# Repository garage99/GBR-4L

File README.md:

# GBR-4L

GBR-4L is a self-powered USB 2.0 carrier for four Semtech (formerly Sierra
Wireless) AirPrime EM7565 LTE modules. It is intended for use with
OpenMPTCProuter and for manufacture by JLCPCB.

## Rev 1.0 baseline

- Four EM7565 modules in M.2 Key B 3042 sockets
- One nano-SIM per modem
- USB 2.0 High-Speed upstream through a USB Type-C receptacle
- Four-port USB 2.0 hub
- 12 V external input
- Four independently controlled 3.3 V modem power rails
- Per-modem `RESET#`, `W_DISABLE1#`, status indication, and test points
- Four-layer PCB: signal / ground / power / signal
- Preferred outline: 160 mm x 100 mm

> EM7565 is an M.2 module, not a Mini PCIe card. The USB Type-C connector is an
> upstream-facing USB device port (UFP), even though it connects to the host PC.

## Repository layout

- `Hardware/KiCad/GBR-4L/` — KiCad 10 project
- `Hardware/Design/` — requirements, design decisions, and interface definitions
- `Hardware/BOM/` — preliminary and released bills of materials
- `Firmware/` — reserved for optional control firmware
- `Case/` — enclosure and mechanical data

## Current milestone

M1 (part selection and electrical architecture) is in progress. The initial
architecture is recorded in
[`Hardware/Design/GBR-4L_Rev1_Design_Baseline.md`](Hardware/Design/GBR-4L_Rev1_Design_Baseline.md).
No Gerber files are released yet.

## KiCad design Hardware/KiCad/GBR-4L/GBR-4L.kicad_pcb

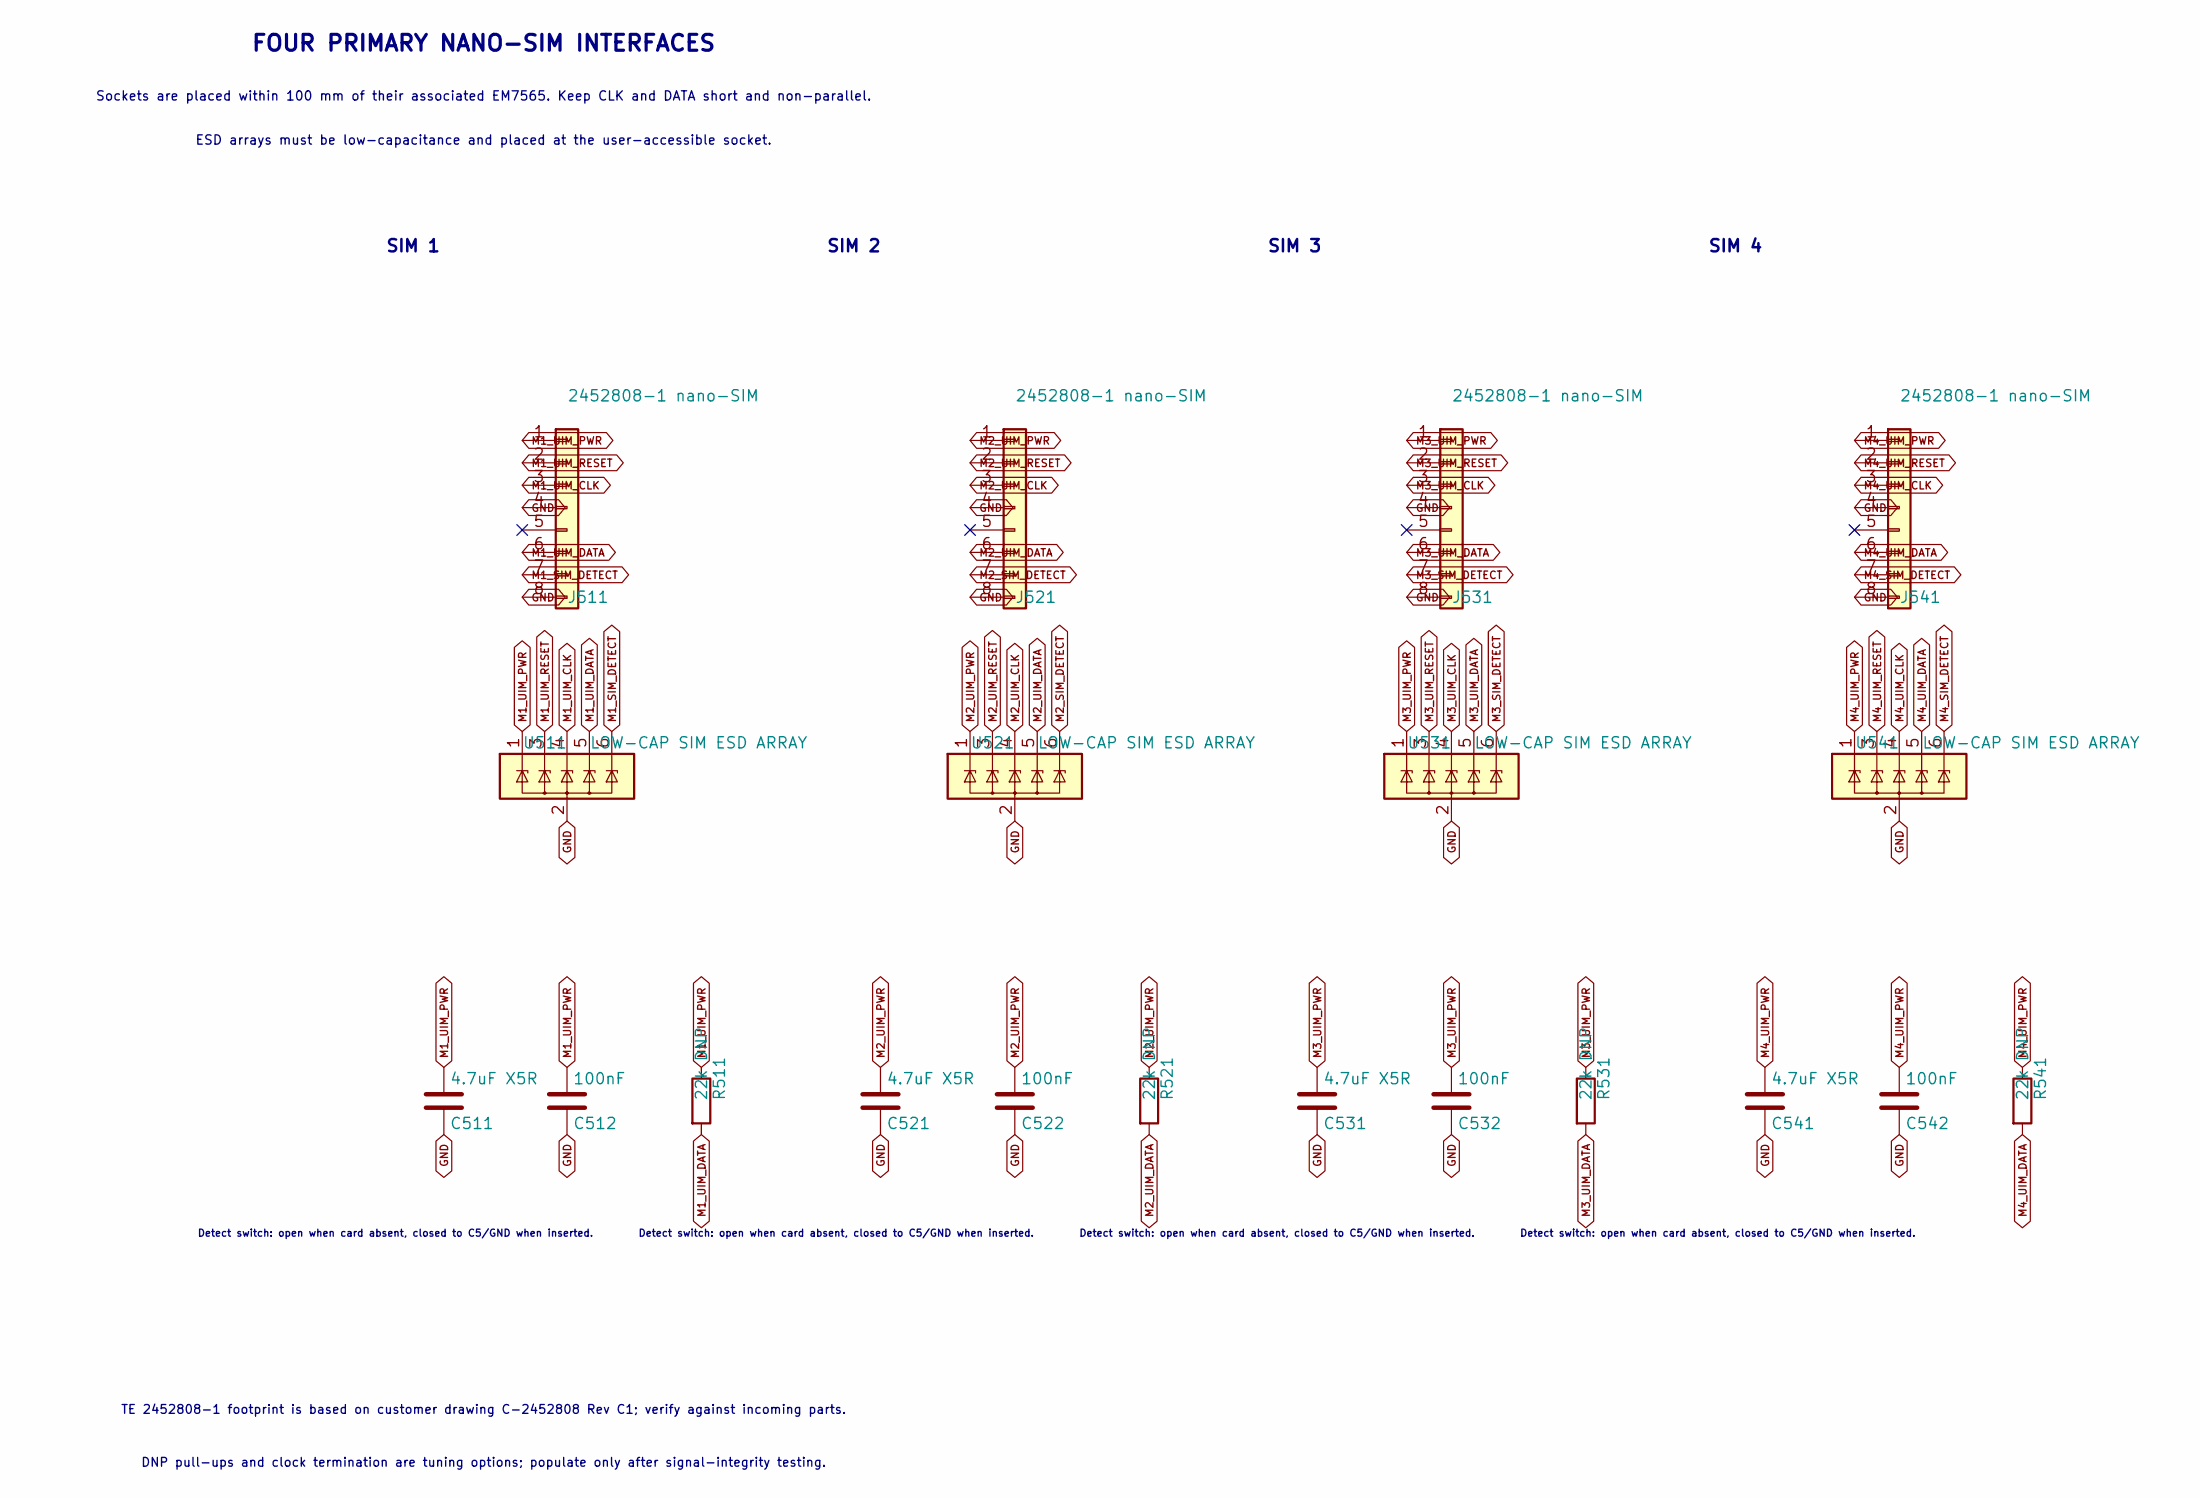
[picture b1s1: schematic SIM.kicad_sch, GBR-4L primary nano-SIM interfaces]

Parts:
C511, C521, C531, C541: 4.7uF X5R; C_0805_2012Metric
C512, C522, C532, C542: 100nF; C_0603_1608Metric
J511, J521, J531, J541: 2452808-1 nano-SIM; TE_2452808-1
R511, R521, R531, R541: 22k DNP; R_0603_1608Metric
U511, U521, U531, U541: LOW-CAP SIM ESD ARRAY; SOT-23-6

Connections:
GND: C511.2, C512.2, C521.2, C522.2, C531.2, C532.2, C541.2, C542.2, J511.4, J511.8, J511.9, J511.10, J511.11, J521.4, J521.8, J521.9, J521.10, J521.11, J531.4, J531.8, J531.9, J531.10, J531.11, J541.4, J541.8, J541.9, J541.10, J541.11, U511.2 (GND), U521.2 (GND), U531.2 (GND), U541.2 (GND); also elsewhere on the board
M1_SIM_DETECT: J511.7, U511.6 (IO5); also elsewhere on the board
M1_UIM_CLK: J511.3, U511.4 (IO3); also elsewhere on the board
M1_UIM_DATA: J511.6, R511.2, U511.5 (IO4); also elsewhere on the board
M1_UIM_PWR: C511.1, C512.1, J511.1, R511.1, U511.1 (IO1); also elsewhere on the board
M1_UIM_RESET: J511.2, U511.3 (IO2); also elsewhere on the board
M2_SIM_DETECT: J521.7, U521.6 (IO5); also elsewhere on the board
M2_UIM_CLK: J521.3, U521.4 (IO3); also elsewhere on the board
M2_UIM_DATA: J521.6, R521.2, U521.5 (IO4); also elsewhere on the board
M2_UIM_PWR: C521.1, C522.1, J521.1, R521.1, U521.1 (IO1); also elsewhere on the board
M2_UIM_RESET: J521.2, U521.3 (IO2); also elsewhere on the board
M3_SIM_DETECT: J531.7, U531.6 (IO5); also elsewhere on the board
M3_UIM_CLK: J531.3, U531.4 (IO3); also elsewhere on the board
M3_UIM_DATA: J531.6, R531.2, U531.5 (IO4); also elsewhere on the board
M3_UIM_PWR: C531.1, C532.1, J531.1, R531.1, U531.1 (IO1); also elsewhere on the board
M3_UIM_RESET: J531.2, U531.3 (IO2); also elsewhere on the board
M4_SIM_DETECT: J541.7, U541.6 (IO5); also elsewhere on the board
M4_UIM_CLK: J541.3, U541.4 (IO3); also elsewhere on the board
M4_UIM_DATA: J541.6, R541.2, U541.5 (IO4); also elsewhere on the board
M4_UIM_PWR: C541.1, C542.1, J541.1, R541.1, U541.1 (IO1); also elsewhere on the board
M4_UIM_RESET: J541.2, U541.3 (IO2); also elsewhere on the board

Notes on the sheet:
SIM 3
ESD arrays must be low-capacitance and placed at the user-accessible socket.
SIM 4
FOUR PRIMARY NANO-SIM INTERFACES
Sockets are placed within 100 mm of their associated EM7565. Keep CLK and DATA short and non-parallel.
SIM 2
Detect switch: open when card absent, closed to C5/GND when inserted.
DNP pull-ups and clock termination are tuning options; populate only after signal-integrity testing.
SIM 1
TE 2452808-1 footprint is based on customer drawing C-2452808 Rev C1; verify against incoming parts.

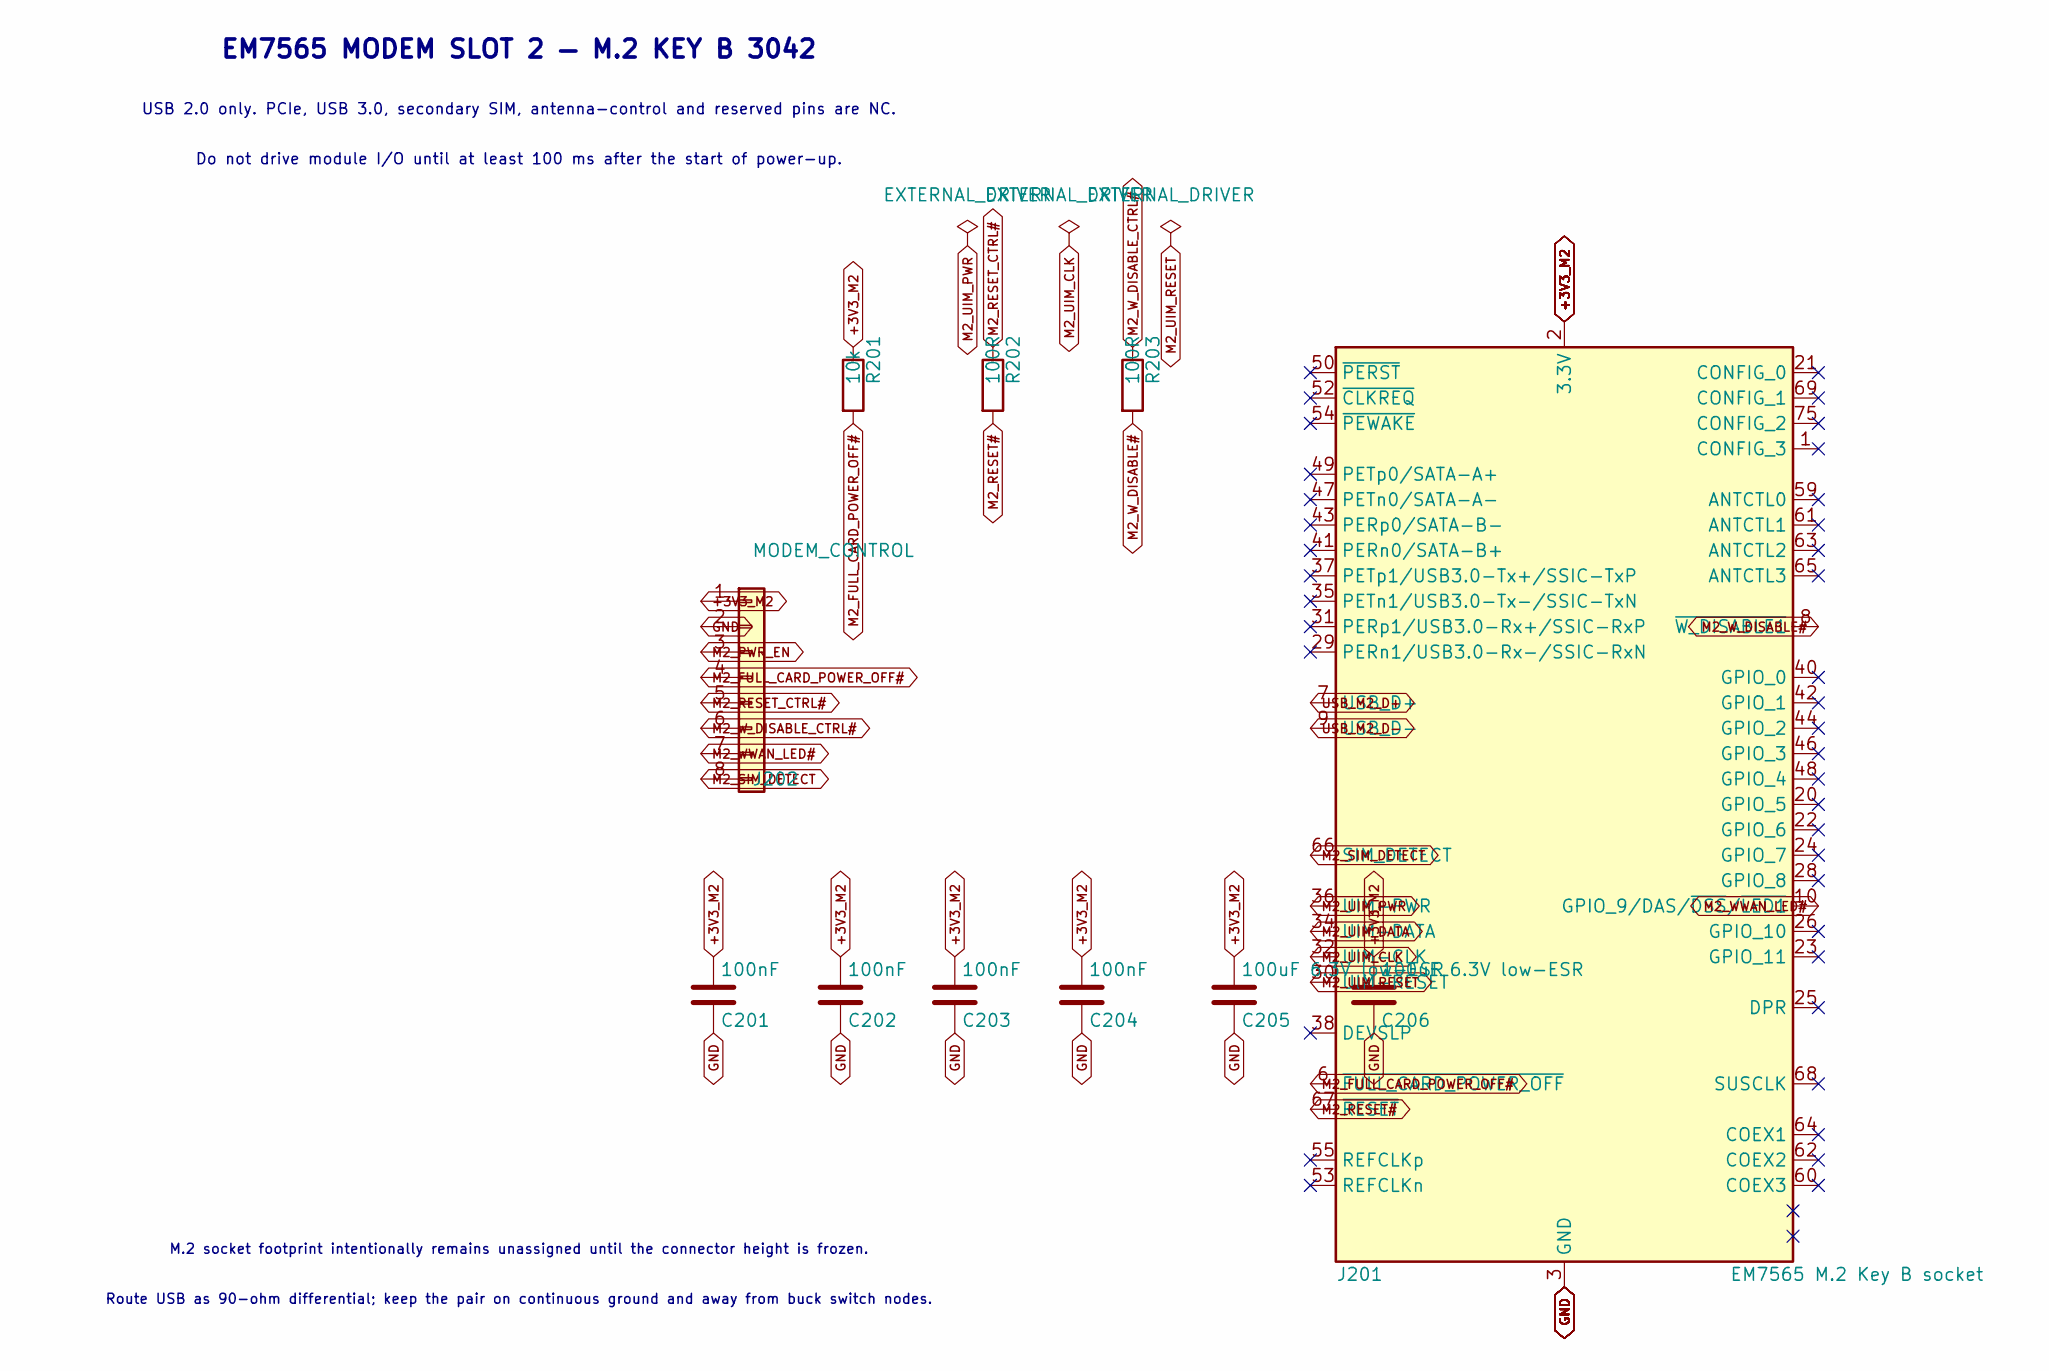
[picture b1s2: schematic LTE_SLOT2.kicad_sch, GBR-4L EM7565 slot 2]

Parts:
C201, C202, C203, C204: 100nF; C_0603_1608Metric
C205, C206: 100uF 6.3V low-ESR; C_1210_3225Metric
J201: EM7565 M.2 Key B socket
J202: MODEM_CONTROL; PinHeader_1x08_P2.54mm_Vertical
R201: 10k; R_0603_1608Metric
R202, R203: 100R; R_0603_1608Metric

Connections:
+3V3_M2: C201.1, C202.1, C203.1, C204.1, C205.1, C206.1, J201.2 (3.3V), J201.4 (3.3V), J201.70 (3.3V), J201.72 (3.3V), J201.74 (3.3V), J202.1, R201.1; also elsewhere on the board
GND: C201.2, C202.2, C203.2, C204.2, C205.2, C206.2, J201.3 (GND), J201.5 (GND), J201.11 (GND), J201.27 (GND), J201.33 (GND), J201.39 (GND), J201.45 (GND), J201.51 (GND), J201.57 (GND), J201.71 (GND), J201.73 (GND), J202.2; also elsewhere on the board
M2_FULL_CARD_POWER_OFF#: J201.6 (~FULL_CARD_POWER_OFF), J202.4, R201.2
M2_PWR_EN: J202.3; also elsewhere on the board
M2_RESET#: J201.67 (~RESET), R202.2
M2_RESET_CTRL#: J202.5, R202.1; also elsewhere on the board
M2_SIM_DETECT: J201.66 (SIM_DETECT), J202.8; also elsewhere on the board
M2_UIM_CLK: J201.32 (UIM-CLK); also elsewhere on the board
M2_UIM_DATA: J201.34 (UIM-DATA); also elsewhere on the board
M2_UIM_PWR: J201.36 (UIM-PWR); also elsewhere on the board
M2_UIM_RESET: J201.30 (UIM-RESET); also elsewhere on the board
M2_WWAN_LED#: J201.10 (GPIO_9/DAS/~DSS/~LED1), J202.7; also elsewhere on the board
M2_W_DISABLE#: J201.8 (~W_DISABLE1), R203.2
M2_W_DISABLE_CTRL#: J202.6, R203.1; also elsewhere on the board
USB_M2_D+: J201.7 (USB_D+); also elsewhere on the board
USB_M2_D-: J201.9 (USB_D-); also elsewhere on the board

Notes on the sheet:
Route USB as 90-ohm differential; keep the pair on continuous ground and away from buck switch nodes.
USB 2.0 only. PCIe, USB 3.0, secondary SIM, antenna-control and reserved pins are NC.
M.2 socket footprint intentionally remains unassigned until the connector height is frozen.
Do not drive module I/O until at least 100 ms after the start of power-up.
EM7565 MODEM SLOT 2 — M.2 KEY B 3042

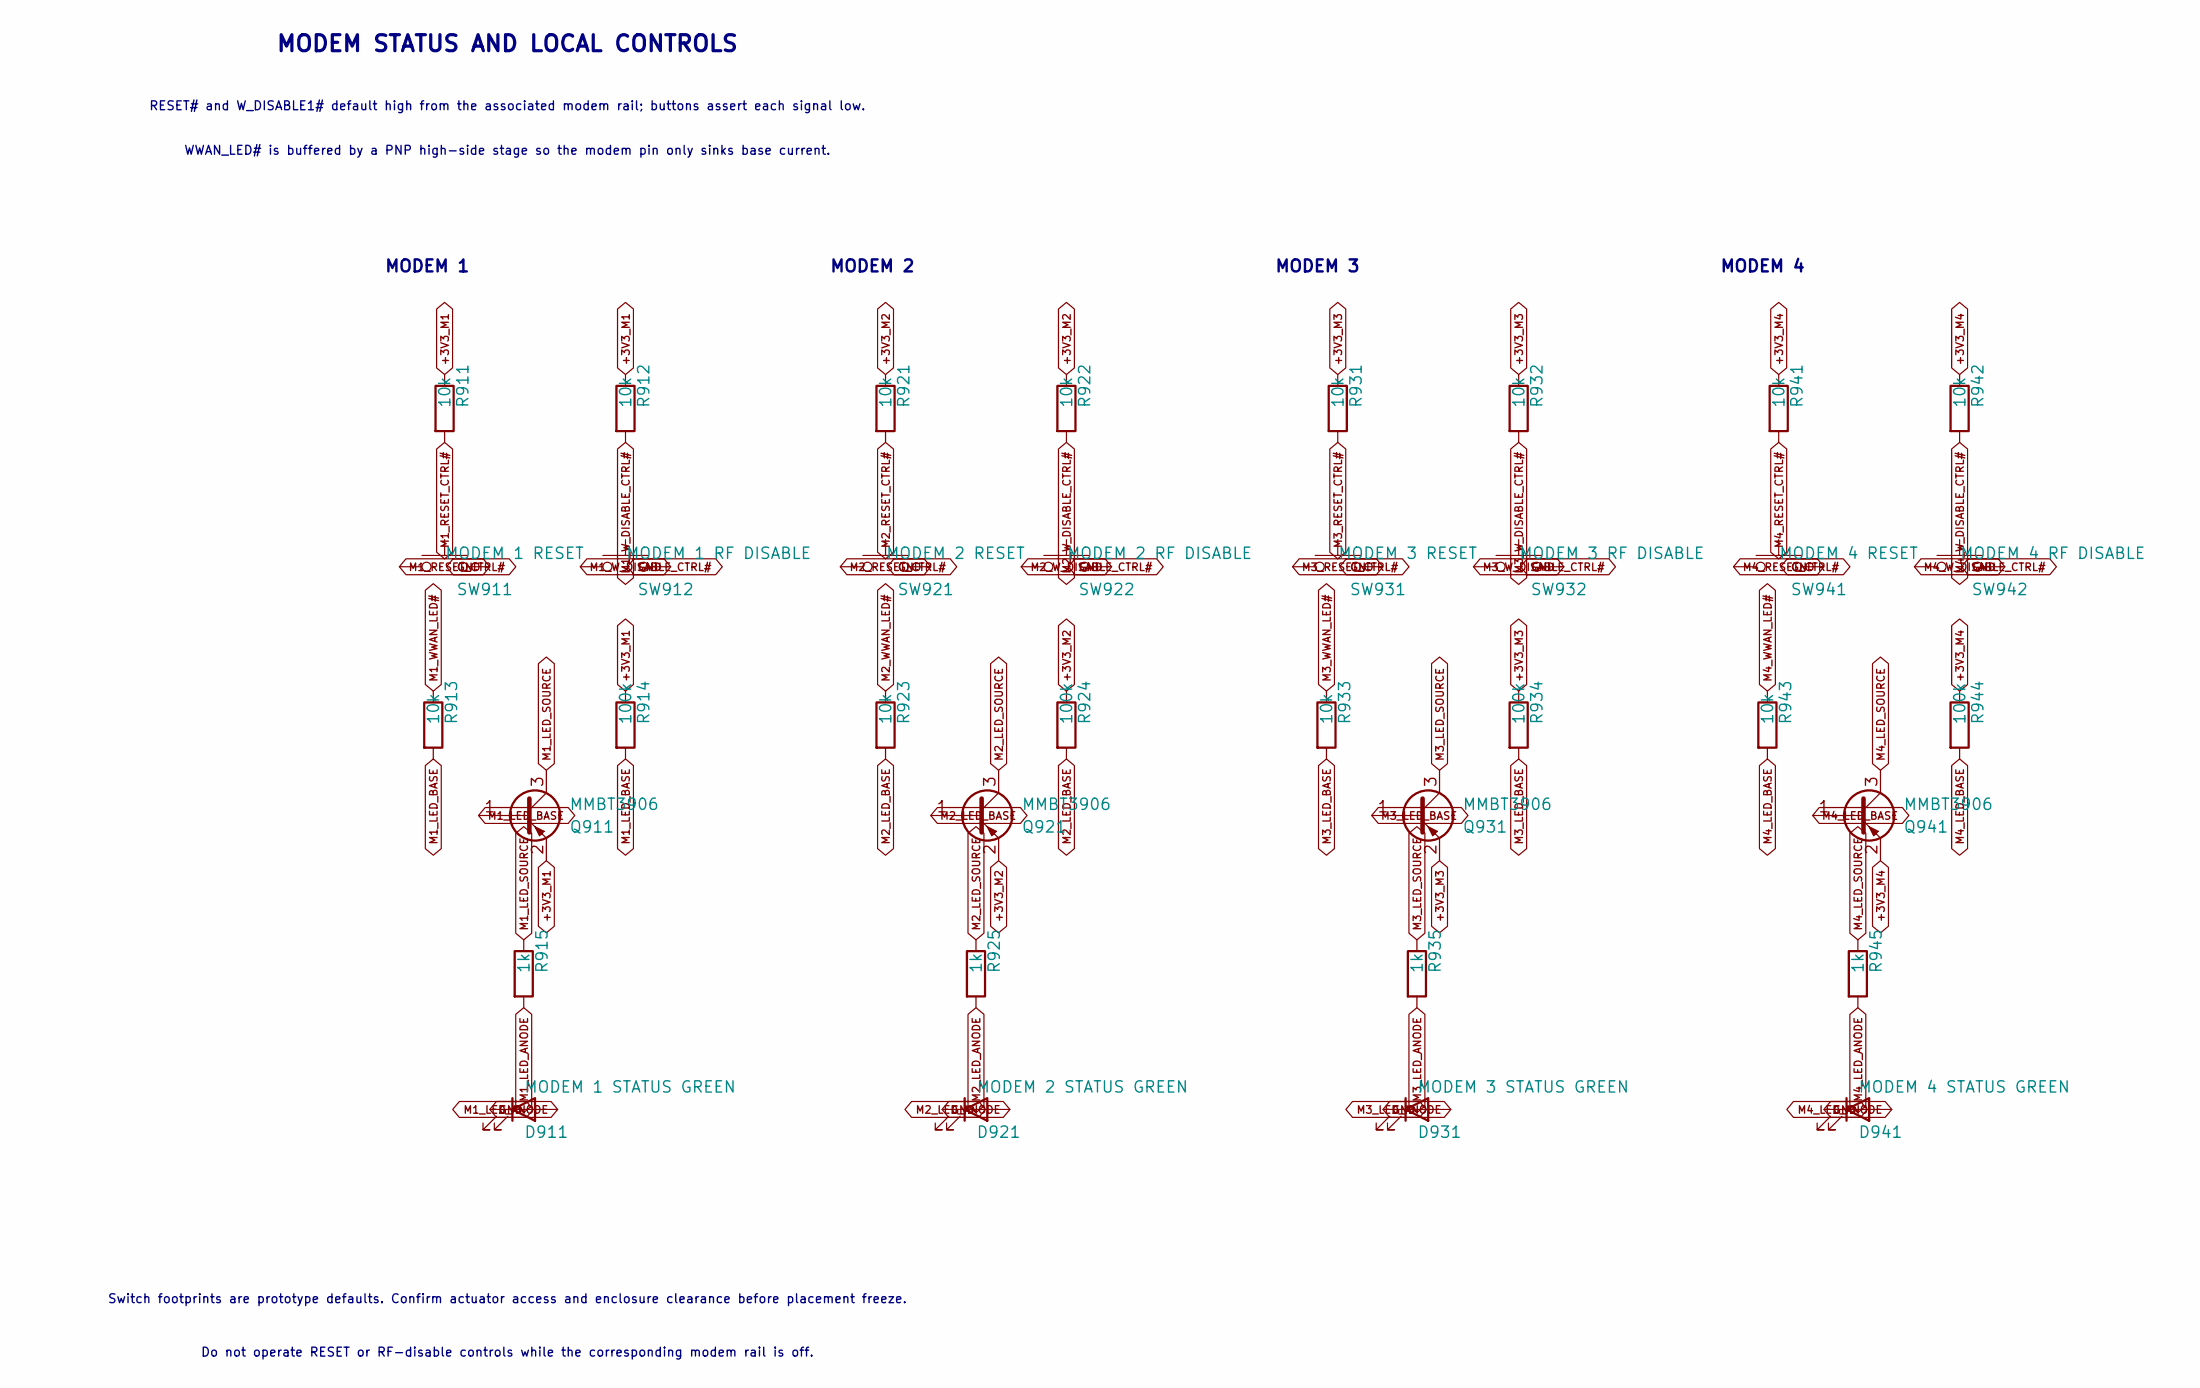
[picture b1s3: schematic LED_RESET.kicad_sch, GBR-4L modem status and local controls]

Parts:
D911: MODEM 1 STATUS GREEN; LED_0603_1608Metric
D921: MODEM 2 STATUS GREEN; LED_0603_1608Metric
D931: MODEM 3 STATUS GREEN; LED_0603_1608Metric
D941: MODEM 4 STATUS GREEN; LED_0603_1608Metric
Q911, Q921, Q931, Q941: MMBT3906; SOT-23
R911, R912, R913, R921, R922, R923, R931, R932, R933, R941, R942, R943: 10k; R_0603_1608Metric
R914, R924, R934, R944: 100k; R_0603_1608Metric
R915, R925, R935, R945: 1k; R_0603_1608Metric
SW911: MODEM 1 RESET; SW_SPST_TL3305A
SW912: MODEM 1 RF DISABLE; SW_SPST_TL3305A
SW921: MODEM 2 RESET; SW_SPST_TL3305A
SW922: MODEM 2 RF DISABLE; SW_SPST_TL3305A
SW931: MODEM 3 RESET; SW_SPST_TL3305A
SW932: MODEM 3 RF DISABLE; SW_SPST_TL3305A
SW941: MODEM 4 RESET; SW_SPST_TL3305A
SW942: MODEM 4 RF DISABLE; SW_SPST_TL3305A

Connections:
+3V3_M1: Q911.2 (E), R911.1, R912.1, R914.1; also elsewhere on the board
+3V3_M2: Q921.2 (E), R921.1, R922.1, R924.1; also elsewhere on the board
+3V3_M3: Q931.2 (E), R931.1, R932.1, R934.1; also elsewhere on the board
+3V3_M4: Q941.2 (E), R941.1, R942.1, R944.1; also elsewhere on the board
GND: D911.1 (K), D921.1 (K), D931.1 (K), D941.1 (K), SW911.2, SW912.2, SW921.2, SW922.2, SW931.2, SW932.2, SW941.2, SW942.2; also elsewhere on the board
M1_LED_ANODE: D911.2 (A), R915.2
M1_LED_BASE: Q911.1 (B), R913.2, R914.2
M1_LED_SOURCE: Q911.3 (C), R915.1
M1_RESET_CTRL#: R911.2, SW911.1; also elsewhere on the board
M1_WWAN_LED#: R913.1; also elsewhere on the board
M1_W_DISABLE_CTRL#: R912.2, SW912.1; also elsewhere on the board
M2_LED_ANODE: D921.2 (A), R925.2
M2_LED_BASE: Q921.1 (B), R923.2, R924.2
M2_LED_SOURCE: Q921.3 (C), R925.1
M2_RESET_CTRL#: R921.2, SW921.1; also elsewhere on the board
M2_WWAN_LED#: R923.1; also elsewhere on the board
M2_W_DISABLE_CTRL#: R922.2, SW922.1; also elsewhere on the board
M3_LED_ANODE: D931.2 (A), R935.2
M3_LED_BASE: Q931.1 (B), R933.2, R934.2
M3_LED_SOURCE: Q931.3 (C), R935.1
M3_RESET_CTRL#: R931.2, SW931.1; also elsewhere on the board
M3_WWAN_LED#: R933.1; also elsewhere on the board
M3_W_DISABLE_CTRL#: R932.2, SW932.1; also elsewhere on the board
M4_LED_ANODE: D941.2 (A), R945.2
M4_LED_BASE: Q941.1 (B), R943.2, R944.2
M4_LED_SOURCE: Q941.3 (C), R945.1
M4_RESET_CTRL#: R941.2, SW941.1; also elsewhere on the board
M4_WWAN_LED#: R943.1; also elsewhere on the board
M4_W_DISABLE_CTRL#: R942.2, SW942.1; also elsewhere on the board

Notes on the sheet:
Do not operate RESET or RF-disable controls while the corresponding modem rail is off.
MODEM 2
WWAN_LED# is buffered by a PNP high-side stage so the modem pin only sinks base current.
RESET# and W_DISABLE1# default high from the associated modem rail; buttons assert each signal low.
MODEM STATUS AND LOCAL CONTROLS
MODEM 4
MODEM 3
MODEM 1
Switch footprints are prototype defaults. Confirm actuator access and enclosure clearance before placement freeze.

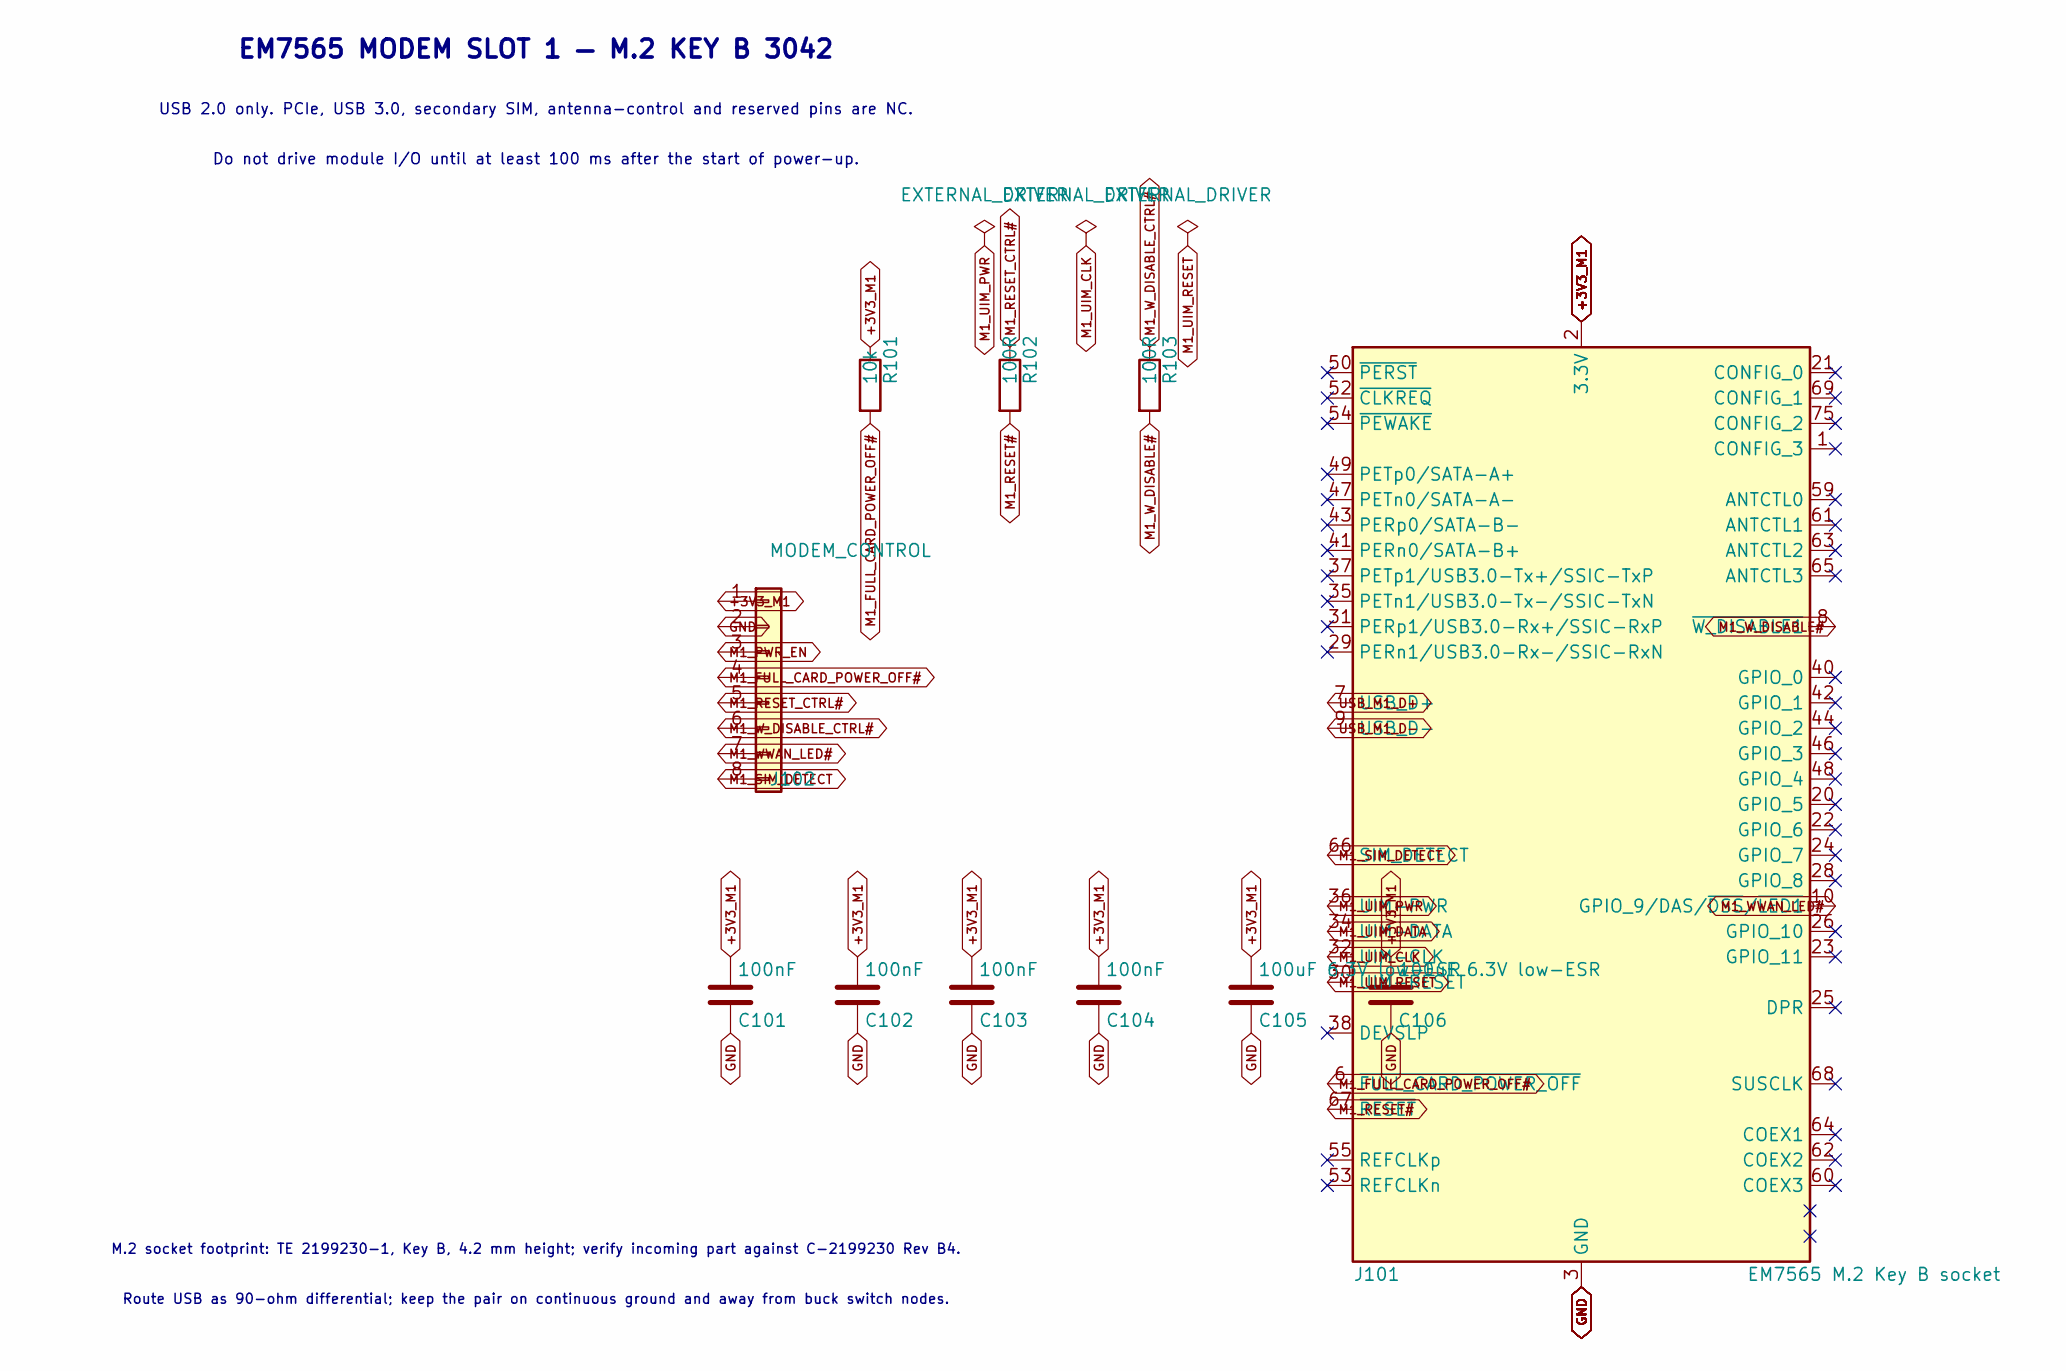
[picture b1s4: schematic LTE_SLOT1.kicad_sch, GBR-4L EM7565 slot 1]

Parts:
C101, C102, C103, C104: 100nF; C_0603_1608Metric
C105, C106: 100uF 6.3V low-ESR; C_1210_3225Metric
J101: EM7565 M.2 Key B socket; TE_2199230-1_M2_Key-B
J102: MODEM_CONTROL; PinHeader_1x08_P2.54mm_Vertical
R101: 10k; R_0603_1608Metric
R102, R103: 100R; R_0603_1608Metric

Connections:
+3V3_M1: C101.1, C102.1, C103.1, C104.1, C105.1, C106.1, J101.2 (3.3V), J101.4 (3.3V), J101.70 (3.3V), J101.72 (3.3V), J101.74 (3.3V), J102.1, R101.1; also elsewhere on the board
GND: C101.2, C102.2, C103.2, C104.2, C105.2, C106.2, J101.3 (GND), J101.5 (GND), J101.11 (GND), J101.27 (GND), J101.33 (GND), J101.39 (GND), J101.45 (GND), J101.51 (GND), J101.57 (GND), J101.71 (GND), J101.73 (GND), J102.2; also elsewhere on the board
M1_FULL_CARD_POWER_OFF#: J101.6 (~FULL_CARD_POWER_OFF), J102.4, R101.2
M1_PWR_EN: J102.3; also elsewhere on the board
M1_RESET#: J101.67 (~RESET), R102.2
M1_RESET_CTRL#: J102.5, R102.1; also elsewhere on the board
M1_SIM_DETECT: J101.66 (SIM_DETECT), J102.8; also elsewhere on the board
M1_UIM_CLK: J101.32 (UIM-CLK); also elsewhere on the board
M1_UIM_DATA: J101.34 (UIM-DATA); also elsewhere on the board
M1_UIM_PWR: J101.36 (UIM-PWR); also elsewhere on the board
M1_UIM_RESET: J101.30 (UIM-RESET); also elsewhere on the board
M1_WWAN_LED#: J101.10 (GPIO_9/DAS/~DSS/~LED1), J102.7; also elsewhere on the board
M1_W_DISABLE#: J101.8 (~W_DISABLE1), R103.2
M1_W_DISABLE_CTRL#: J102.6, R103.1; also elsewhere on the board
USB_M1_D+: J101.7 (USB_D+); also elsewhere on the board
USB_M1_D-: J101.9 (USB_D-); also elsewhere on the board

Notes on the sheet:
Do not drive module I/O until at least 100 ms after the start of power-up.
M.2 socket footprint: TE 2199230-1, Key B, 4.2 mm height; verify incoming part against C-2199230 Rev B4.
EM7565 MODEM SLOT 1 — M.2 KEY B 3042
USB 2.0 only. PCIe, USB 3.0, secondary SIM, antenna-control and reserved pins are NC.
Route USB as 90-ohm differential; keep the pair on continuous ground and away from buck switch nodes.
